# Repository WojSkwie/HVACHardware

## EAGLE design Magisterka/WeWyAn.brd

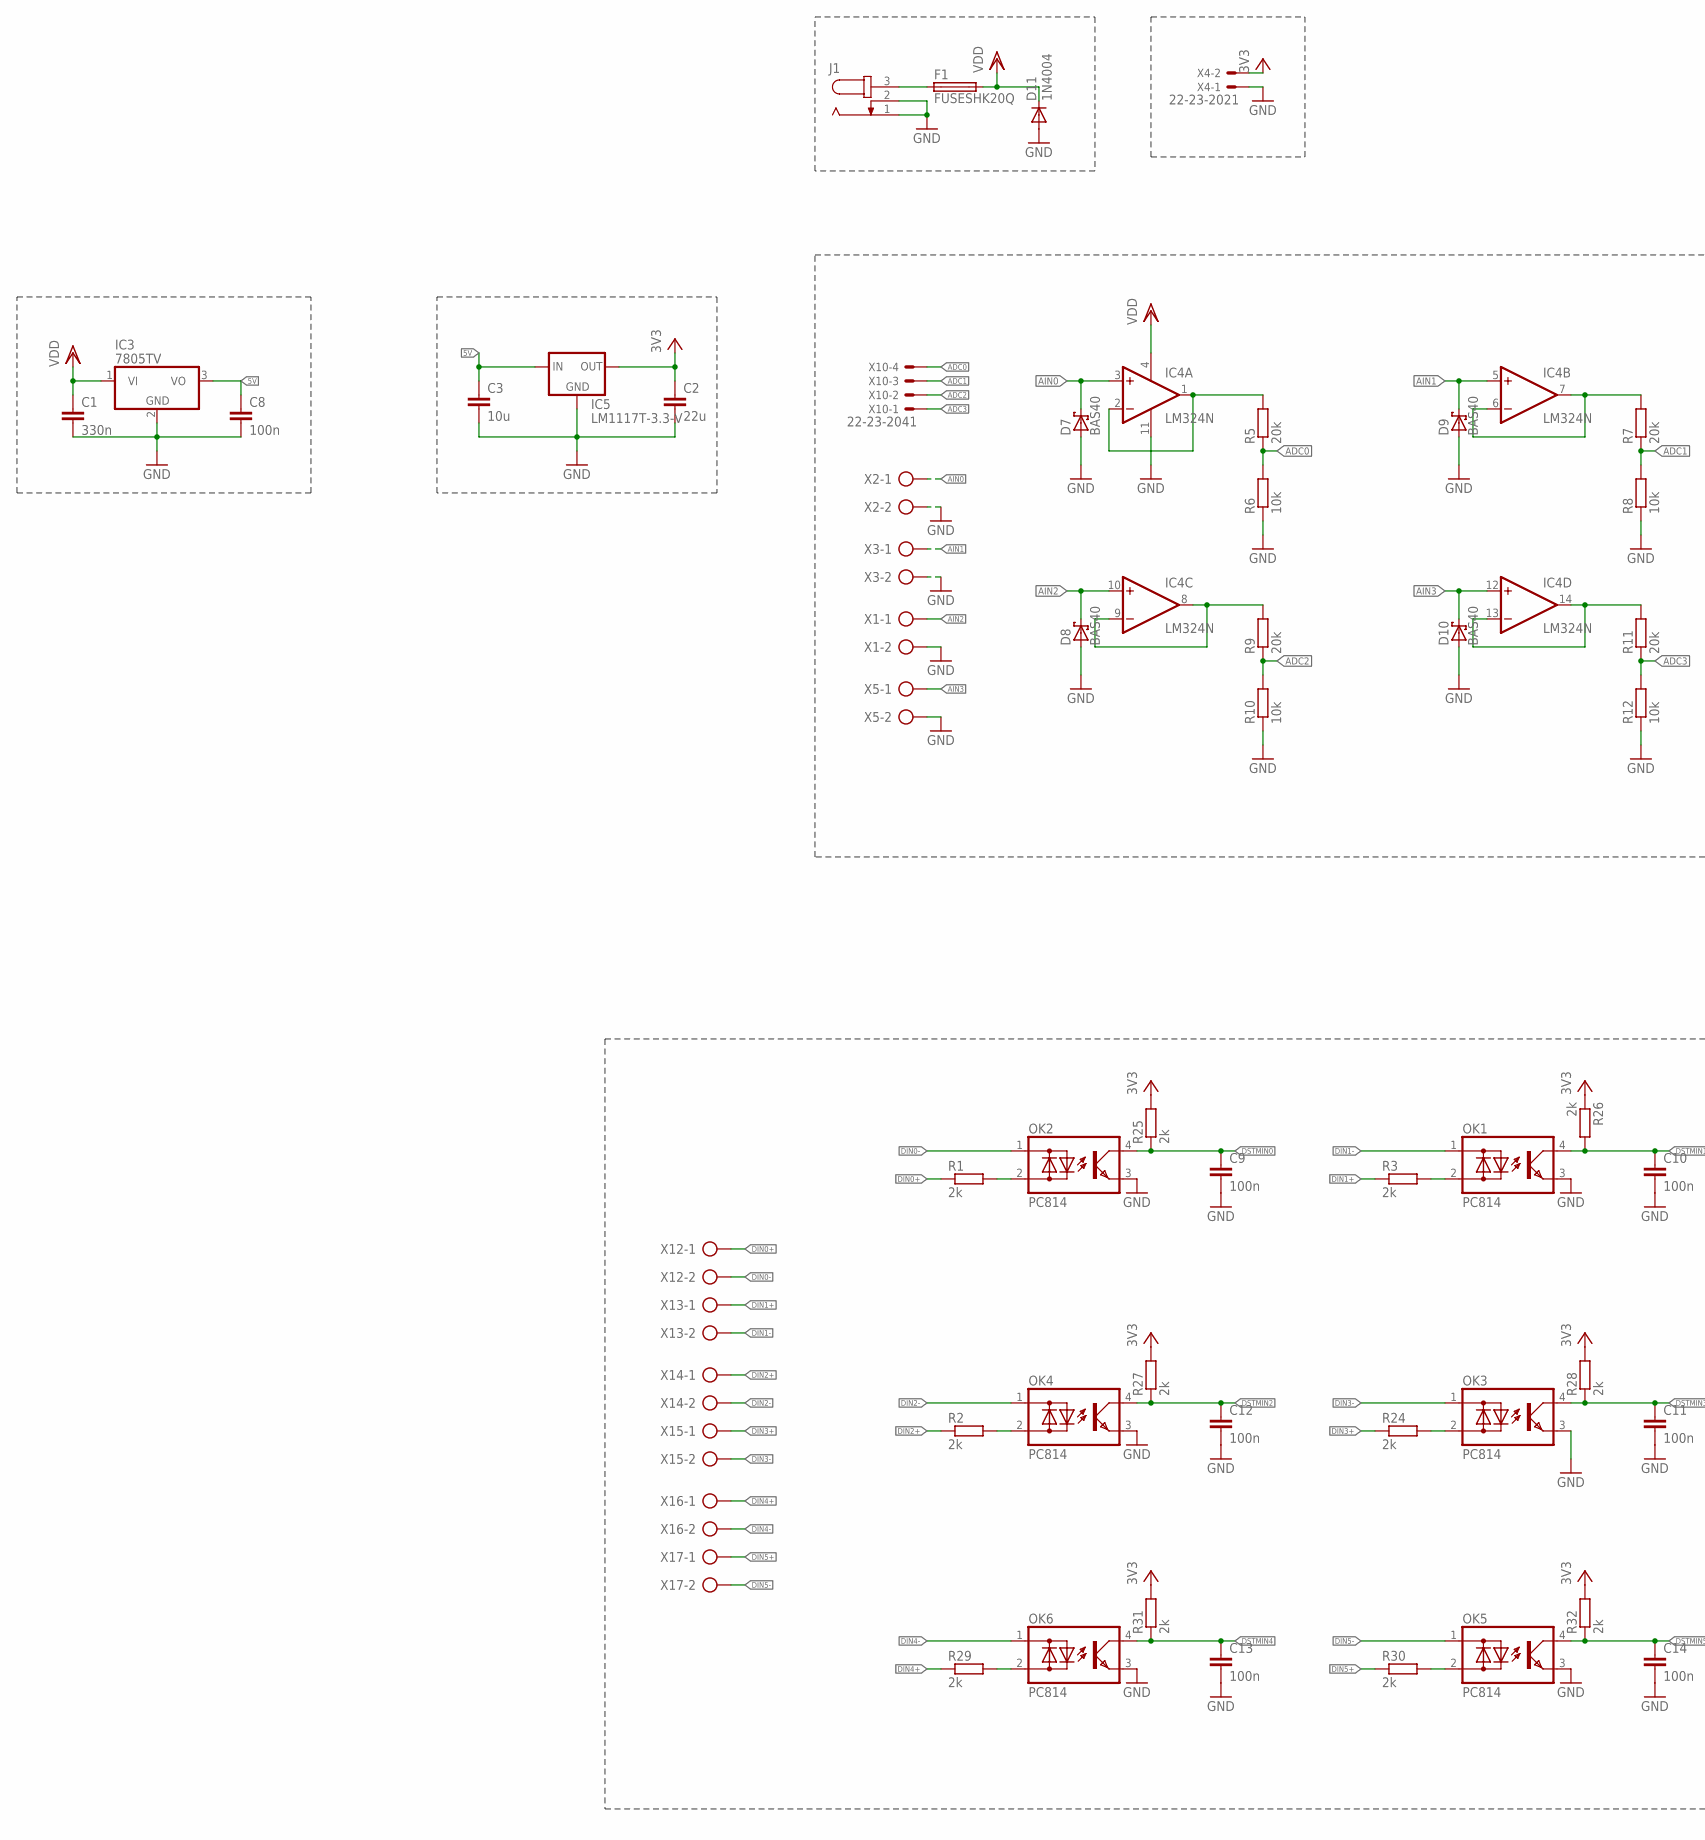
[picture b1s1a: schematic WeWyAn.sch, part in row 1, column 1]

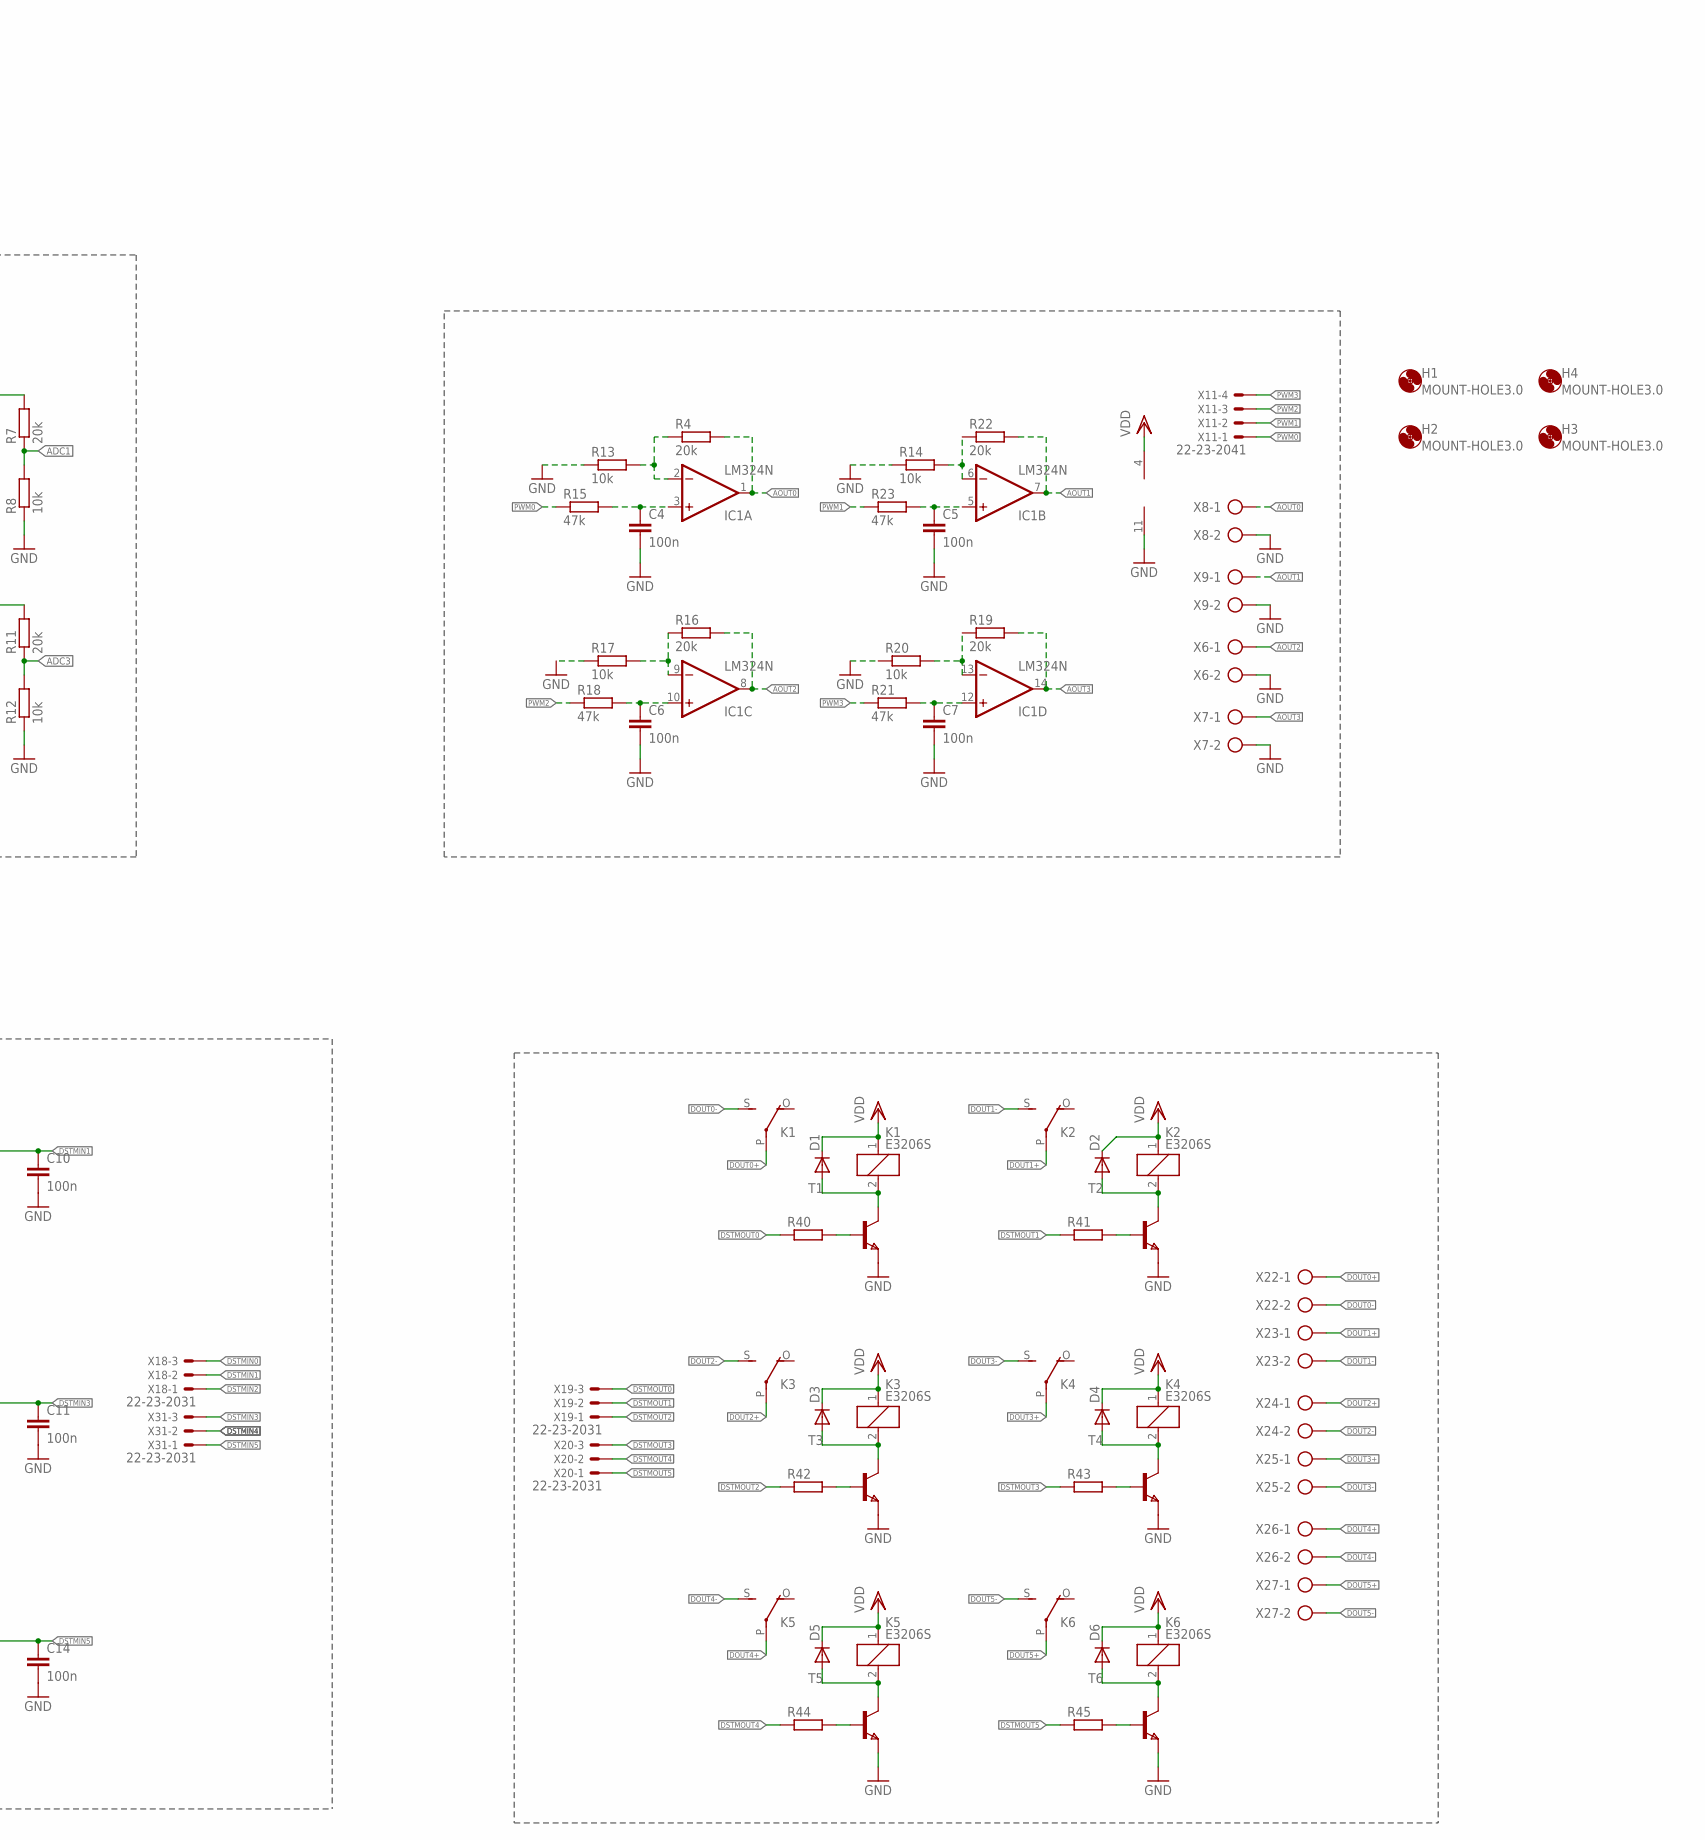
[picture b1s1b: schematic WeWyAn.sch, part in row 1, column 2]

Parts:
C1: 330n; C0603
C2: 22u; C0603K
C3: 10u; C0603K
C4, C5, C6, C7: 100n; C0603K
C8, C9, C10, C11, C12, C13, C14: 100n; C0603
D1, D2, D3, D4, D5, D6: DIODE-DO214AC; DO214AC
D7, D8, D9, D10: BAS40; SOT23
D11: 1N4004; DO41-10
F1: FUSESHK20Q; SHK20Q
H1, H2, H3, H4: MOUNT-HOLE3.0; 3,0
IC1, IC4: LM324N; DIL14
IC3: 7805TV; TO220V
IC5: LM1117T-3.3-V; TO220V
J1: JACK-PLUG1; SPC4078
K1, K2, K3, K4, K5, K6: E3206S
OK1, OK2, OK3, OK4, OK5, OK6: PC814; DIL04
R1, R2, R3, R24, R25, R26, R27, R28, R29, R30, R31, R32: 2k; R0603
R4, R5, R7, R9, R11, R16, R19, R22: 20k; R0603
R6, R8, R10, R12, R13, R14, R17, R20: 10k; R0603
R15, R18, R21, R23: 47k; R0603
R40, R41, R42, R43, R44, R45: R-EU_R0603; R0603
T1, T2, T3, T4, T5, T6: NPNSOT223; SOT223
X1, X2, X3, X5, X6, X7, X8, X9, X12, X13, X14, X15, X16, X17, X22, X23, X24, X25, X26, X27: AK500/2-H
X4: 22-23-2021
X10, X11: 22-23-2041
X18, X19, X20, X31: 22-23-2031

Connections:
5V: C3.1, C8.1, IC3.3 (VO), IC5.3 (IN)
ADC0: R5.1, R6.2, X10.4
ADC1: R7.1, R8.2, X10.3
ADC2: R9.1, R10.2, X10.2
ADC3: R11.1, R12.2, X10.1
AIN0: D7.3 (C), IC4.3 (+IN), X2.1
AIN1: D9.3 (C), IC4.5 (+IN), X3.1
AIN2: D8.3 (C), IC4.10 (+IN), X1.1
AIN3: D10.3 (C), IC4.12 (+IN), X5.1
AOUT0: IC1.1 (OUT), R4.2, X8.1
AOUT1: IC1.7 (OUT), R22.2, X9.1
AOUT2: IC1.8 (OUT), R16.2, X6.1
AOUT3: IC1.14 (OUT), R19.2, X7.1
DIN0+: R1.1, X12.1
DIN0-: OK2.1 (AC1), X12.2
DIN1+: R3.1, X13.1
DIN1-: OK1.1 (AC1), X13.2
DIN2+: R2.1, X14.1
DIN2-: OK4.1 (AC1), X14.2
DIN3+: R24.1, X15.1
DIN3-: OK3.1 (AC1), X15.2
DIN4+: R29.1, X16.1
DIN4-: OK6.1 (AC1), X16.2
DIN5+: R30.1, X17.1
DIN5-: OK5.1 (AC1), X17.2
DOUT0+: K1.P, X22.1
DOUT0-: K1.S, X22.2
DOUT1+: K2.P, X23.1
DOUT1-: K2.S, X23.2
DOUT2+: K3.P, X24.1
DOUT2-: K3.S, X24.2
DOUT3+: K4.P, X25.1
DOUT3-: K4.S, X25.2
DOUT4+: K5.P, X26.1
DOUT4-: K5.S, X26.2
DOUT5+: K6.P, X27.1
DOUT5-: K6.S, X27.2
DSTMIN0: C9.1, OK2.4 (C), R25.1, X18.3
DSTMIN1: C10.1, OK1.4 (C), R26.2, X18.2
DSTMIN2: C12.1, OK4.4 (C), R27.1, X18.1
DSTMIN3: C11.1, OK3.4 (C), R28.1, X31.3
DSTMIN4: C13.1, OK6.4 (C), R31.1, X31.2
DSTMIN5: C14.1, OK5.4 (C), R32.1, X31.1
DSTMOUT0: R40.1, X19.3
DSTMOUT1: R41.1, X19.2
DSTMOUT2: R42.1, X19.1
DSTMOUT3: R43.1, X20.3
DSTMOUT4: R44.1, X20.2
DSTMOUT5: R45.1, X20.1
GND: C1.2, C2.2, C3.2, C4.2, C5.2, C6.2, C7.2, C8.2, C9.2, C10.2, C11.2, C12.2, C13.2, C14.2, D7.1 (A), D8.1 (A), D9.1 (A), D10.1 (A), D11.A, IC1.11 (V-), IC3.2 (GND), IC4.11 (V-), IC5.1 (GND), J1.1, J1.2, OK1.3 (E), OK2.3 (E), OK3.3 (E), OK4.3 (E), OK5.3 (E), OK6.3 (E), R6.1, R8.1, R10.1, R12.1, R13.1, R14.1, R17.1, R20.1, T1.3 (E), T2.3 (E), T3.3 (E), T4.3 (E), T5.3 (E), T6.3 (E), X1.2, X2.2, X3.2, X4.1, X5.2, X6.2, X7.2, X8.2, X9.2
MINUS0: IC4.1 (OUT), IC4.2 (-IN), R5.2
MINUS1: IC4.6 (-IN), IC4.7 (OUT), R7.2
MINUS2: IC4.8 (OUT), IC4.9 (-IN), R9.2
MINUS3: IC4.13 (-IN), IC4.14 (OUT), R11.2
unnamed: IC1.2 (-IN), R4.1, R13.2
unnamed: OK2.2 (AC2), R1.2
unnamed: C4.1, IC1.3 (+IN), R15.2
unnamed: C6.1, IC1.10 (+IN), R18.2
unnamed: OK1.2 (AC2), R3.2
unnamed: IC1.9 (-IN), R16.1, R17.2
unnamed: IC1.13 (-IN), R19.1, R20.2
unnamed: IC1.6 (-IN), R14.2, R22.1
unnamed: OK3.2 (AC2), R24.2
unnamed: OK4.2 (AC2), R2.2
unnamed: C7.1, IC1.12 (+IN), R21.2
unnamed: F1.1A (1), J1.3
unnamed: C5.1, IC1.5 (+IN), R23.2
unnamed: OK5.2 (AC2), R30.2
unnamed: OK6.2 (AC2), R29.2
unnamed: R40.2, T1.1 (B)
unnamed: D1.A, K1.2, T1.2 (C), T1.4 (C)
unnamed: R41.2, T2.1 (B)
unnamed: R43.2, T4.1 (B)
unnamed: D2.A, K2.2, T2.2 (C), T2.4 (C)
unnamed: R42.2, T3.1 (B)
unnamed: D3.A, K3.2, T3.2 (C), T3.4 (C)
unnamed: R44.2, T5.1 (B)
unnamed: D4.A, K4.2, T4.2 (C), T4.4 (C)
unnamed: R45.2, T6.1 (B)
unnamed: D5.A, K5.2, T5.2 (C), T5.4 (C)
unnamed: D6.A, K6.2, T6.2 (C), T6.4 (C)
PWM0: R15.1, X11.1
PWM1: R23.1, X11.2
PWM2: R18.1, X11.3
PWM3: R21.1, X11.4
VCC: C2.1, IC5.2 (OUT), R25.2, R26.1, R27.2, R28.2, R31.2, R32.2, X4.2
VDD: C1.1, D1.C, D2.C, D3.C, D4.C, D5.C, D6.C, D11.C, F1.2A (2), IC1.4 (V+), IC3.1 (VI), IC4.4 (V+), K1.1, K2.1, K3.1, K4.1, K5.1, K6.1

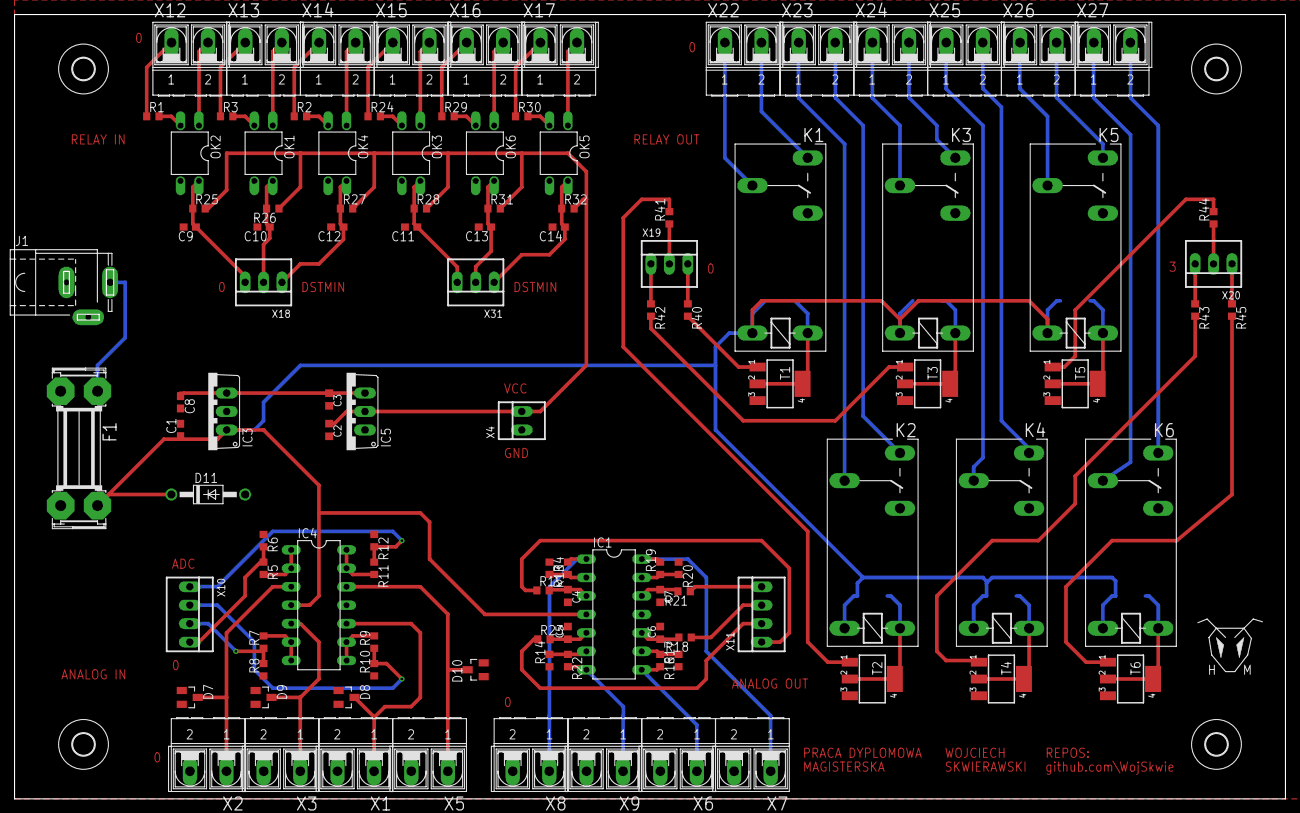
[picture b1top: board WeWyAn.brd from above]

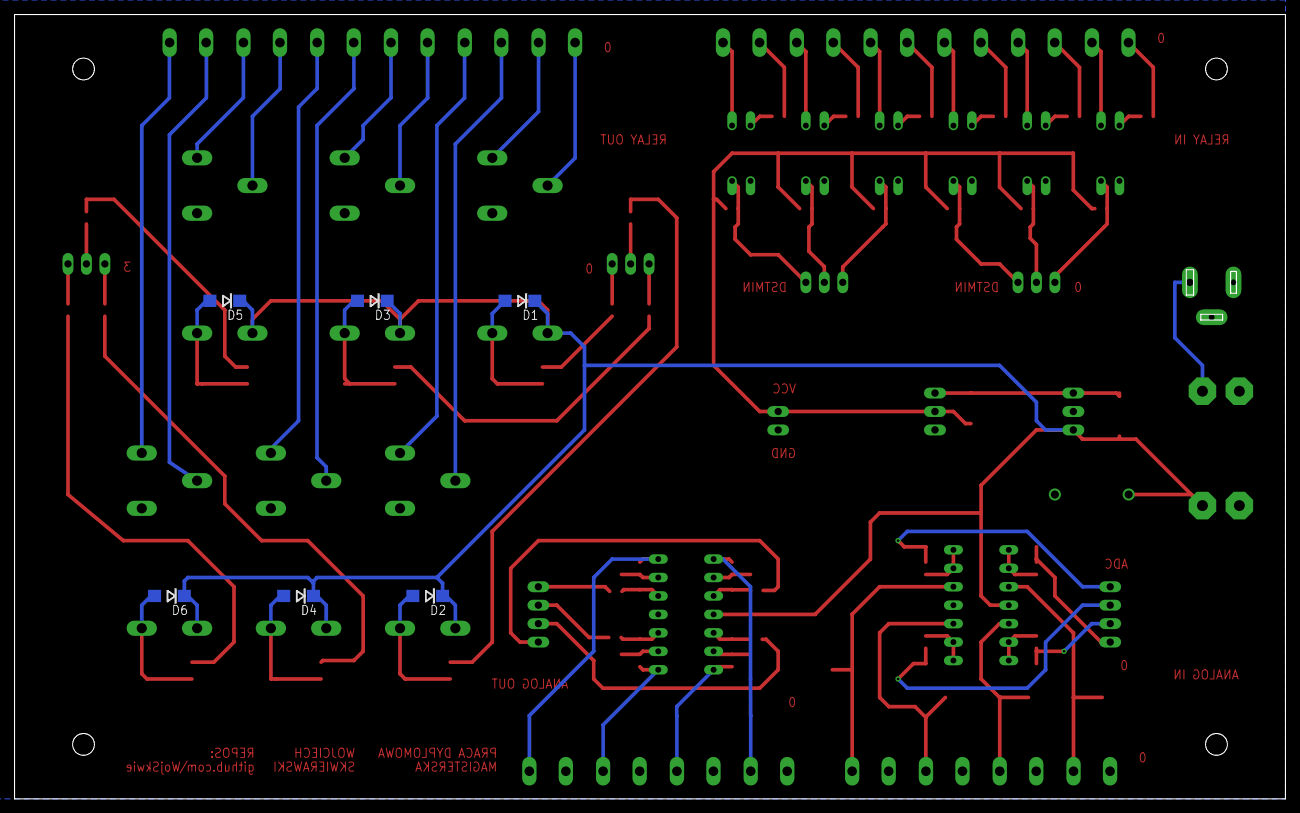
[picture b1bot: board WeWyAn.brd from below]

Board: 2 copper layers, 175.0 x 108.0 mm, 118 parts (6 on the bottom side), 87 nets.

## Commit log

2018-06-20 Added board
2018-06-20 Most of digital part in schematics
2018-06-20 Pinswap in PWM CRIMP and moved several components
2018-06-20 first final
2018-06-20 size changes
2018-06-21 Added relays
2018-06-21 second final
2018-06-26 Few small changed and added gerbers
